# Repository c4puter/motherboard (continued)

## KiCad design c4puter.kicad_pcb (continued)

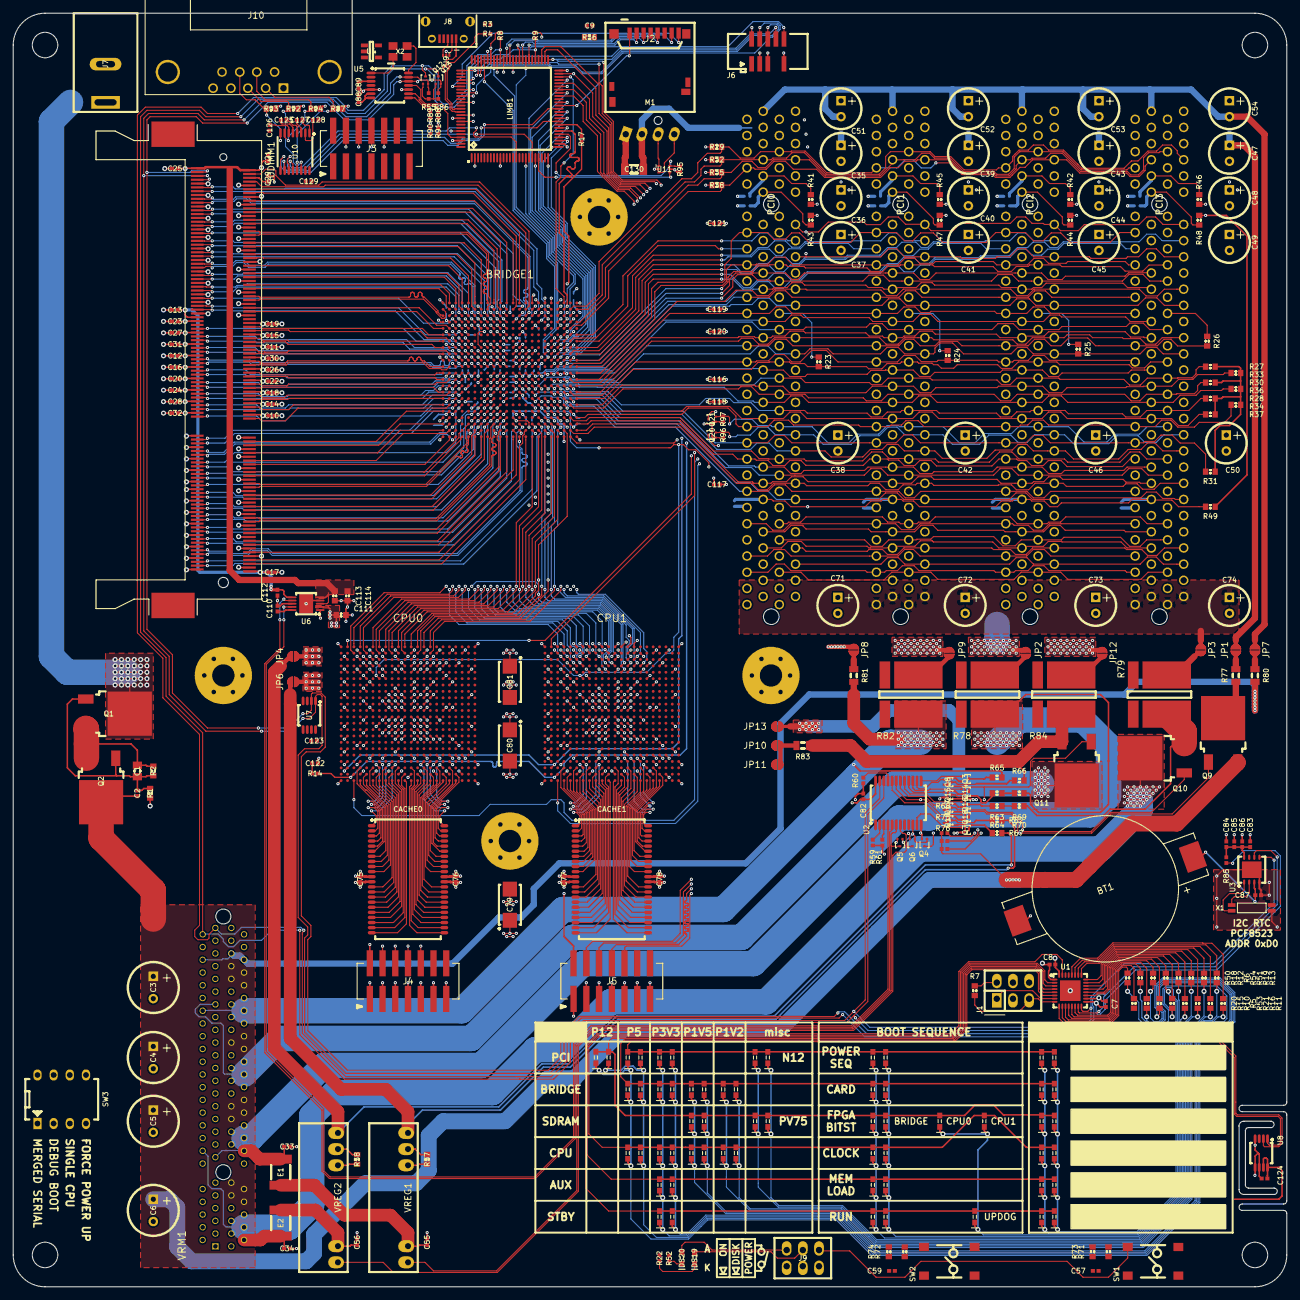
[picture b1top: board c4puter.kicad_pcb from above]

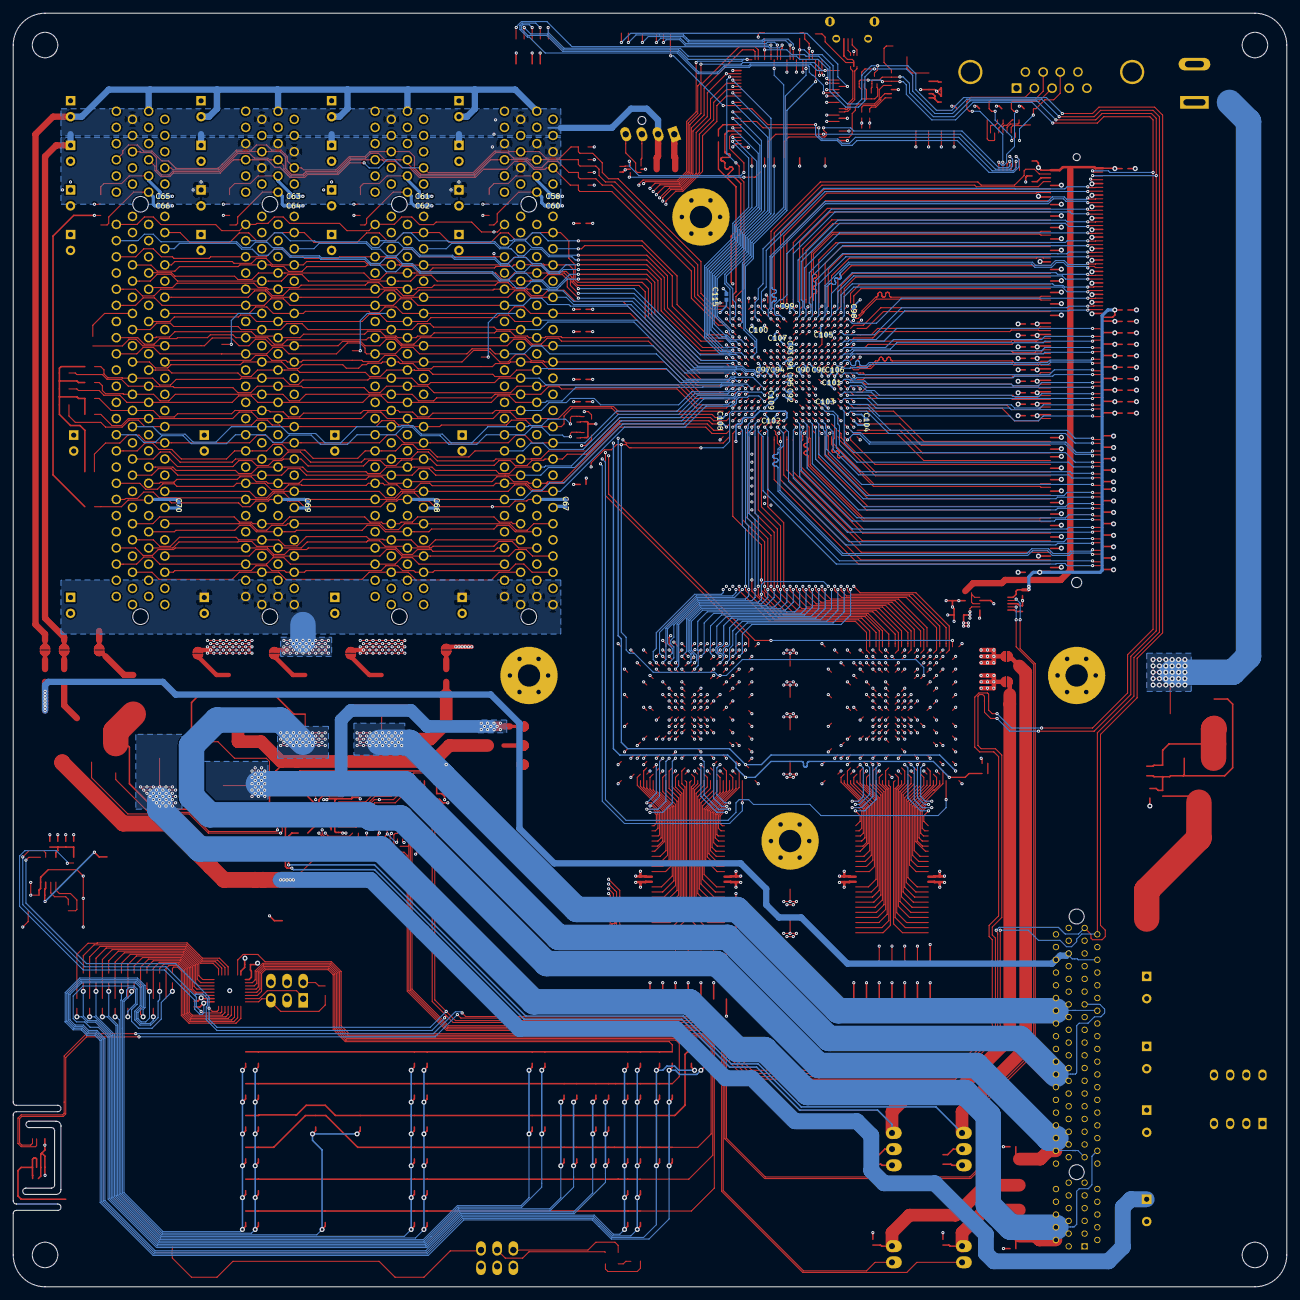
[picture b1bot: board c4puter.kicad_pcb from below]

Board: 6 copper layers, 200.0 x 200.0 mm, 374 parts (40 on the bottom side), 538 nets.

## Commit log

2016-07-06 Finish power supplies
2016-07-06 Upgrade FPGA size, re-route SDRAM
2016-07-06 More PCI work
2016-07-06 Continue routing PCI
2016-07-06 Begin implementing PCI
2016-07-06 Begin replacing power supply
2016-07-06 More power supply work
2016-07-06 PCI bus decoupling
2016-07-06 Uh, more misc work.
2016-07-07 MOAR WORK
2016-07-09 MOAR WORK, v2
2016-07-09 Rip up SDRAM and rotate FPGA
2016-07-10 Reroute SDRAM after bank swap
2016-07-10 Route EC and half of PCI bus to bridge
2016-07-10 Finish routing PCI
2016-07-10 Break out CPU bus
2016-07-10 Add temporary CPU bus pinout file
2016-07-22 workworkwork
2016-07-22 workworkworkwork
2016-07-24 Route CPU bus and cache
2016-07-29 power, yo
2016-08-01 TODO: learn to write good commit messages
2016-08-01 Rearrange power control circuit
2016-08-02 Route clocks
2016-08-02 Proper coin cell holder
2016-08-03 MOAR ROUTING
2016-08-03 Change USB input circuit
2016-08-04 Add RS-232
2016-08-05 Add CPU fan
2016-08-05 Add SDRAM SPD to I2C
2016-08-05 Replace ULN2003 with FETs
2016-08-05 Route PCI SMBUS
2016-08-05 Route PCI utility lines
2016-08-05 Quick TODO revision
2016-08-05 Add configuration pullup resistors
2016-08-05 Tidy up page Power
2016-08-06 Tidy up Power Distribution page
2016-08-06 Approve PCI page with no tidying
2016-08-06 Rename Multibridge to Northbridge
2016-08-06 Tidy up Northbridge sheet
2016-08-06 Tidy up Misc sheet
2016-08-06 Tidy up EC sheet
2016-08-06 Rename EC sheet to LIMB
2016-08-06 Tidy up CPU sheet
2016-08-06 Tidy up Blinkenlights sheet
2016-08-06 Tidy up root sheet
2016-08-06 gitignore .bck files
2016-08-06 Rename project to 'motherboard'
2016-08-06 Fix voltage regulator trim resistors
2016-08-06 Remove unneeded discharge FETs
    PCF8575 can sink the current directly
2016-08-06 Finish adding config interface pullups
2016-08-06 Route FPGA suspend signals
2016-08-06 Add inter-CPU handshake lines
2016-08-06 Move voltage sense to after power routing
2016-08-06 Fix footprint errors and adjust DE-9 footprint
2016-08-06 Check SD and power footprints
2016-08-06 Finish LIMB-SD interface
2016-08-06 Switch resistors to 0402
2016-08-07 Label LIMB sheet
2016-08-08 Rename active-low signals for consistency
2016-08-08 Connect SDRAM EVENT# line
2016-08-08 Route unused PCI JTAG lines
2016-08-10 Add voltage reference
2016-08-10 Update schlib
2016-08-10 Gather and assign all I2C addresses
2016-08-10 Route I2C to CPUs for debug/boot control
    This will provide an interface for the LIMB to write to CPU registers, which
    will be required at least for configuring the program counter at boot.
2016-08-10 Add items to todo list
2016-08-11 Set I2C pullups
2016-08-11 Switch to 8-position DIP switch
2016-08-11 Put clock battery at 180deg orientation for mewyn.
2016-08-11 Add high-speed termination to FPGA config data
    Simulation shows this damping refections.
2016-08-11 Connect RTC alarm interrupt
2016-08-11 Add power connector for storage device
2016-08-11 Set DIP switch part number and courtyard
2016-08-11 IO expander for switches/buttons/LEDs
2016-08-11 Route P3V3_SUSP
2016-08-11 Route P3V3_AUX and some ground
2016-08-11 Route P3V3_BRIDGE
2016-08-11 Route P3V3_CPU
2016-08-11 Add copper fills for connections to VRM
2016-08-11 Route ground
2016-08-11 Route ground, some routing cleanups
2016-08-12 Misc DRC and connectivity fixes
2016-08-12 CPU decoupling
2016-08-12 More power/decoupling
2016-08-12 Add CPUID resistors
2016-08-12 Layer 4 planes
2016-08-12 Route and decouple SDRAM VREF for bridge
2016-08-12 Rest of the planes
2016-08-12 Thermal pads
2016-08-12 Add voltage sense for several rails
2016-08-12 Run ERC and connect missing D6
2016-08-12 Ground plane touchups
2016-08-12 Length-tune SDRAM
2016-08-12 Add more mounting holes
2016-08-12 Length-tune PCI and CPU buses
2016-08-12 Renumber sheets
2016-08-13 Squiggles! Silk!
2016-08-13 Initial BOM
2016-08-14 Final BOM
2016-08-14 Add damping resistor to power input circuit
2016-08-16 Fuck. Rip up bridge.
2016-08-19 Add layer legend
2016-08-19 Fix mechanical pads on SODIMM
2016-08-19 Remove current sense resistors, add I2C debug header
2016-08-19 Via stitching around ground input
2016-08-19 Routing cleanups
2016-08-20 Switch LED metrix driver
2016-08-20 SDRAM take 3: initial breakout
2016-08-21 sdram weeeee
2016-08-23 Reroute CPU bus
2016-08-23 Length-match SDRAM....again
2016-08-25 Route some PCIs
2016-08-28 Route PCI bus. again.
2016-08-29 Redecoupling
2016-08-29 Route bridge JTAG
2016-08-31 Finish most redone routing
2016-08-31 Adjust aux signals, tune FPGA config track lengths
2016-08-31 Fixup PCI power
2016-08-31 Hide silkscreen for 0201 capacitors
2016-08-31 Add some test points
2016-08-31 Add ground clips
2016-09-01 Rearrange LEDs a bit, switch to al-poly caps
2016-09-01 Add some labels
2016-09-01 Make shit pass DRC
2016-09-01 Fix more shit for to pass ERC
2016-09-04 Fix fuckup 2: bank 0 ain't got no SSTL
2016-09-04 Add power input protection
    - Add a fast-blow 6A fuse
    - Specify an optional slow-blow if the fast-blow blows
    - Add snubber near input to damp resonances and prevent spikes
2016-09-05 Redo SDRAM, CPU length matching
2016-09-05 Beeeeeeeeeeeeeeeeeeeeeeeeeeeeeeeeep
2016-09-05 Tidy up a bit
2016-09-05 Final touchup, DRC, render for fab
2016-09-06 Fucking KiCad
2016-09-16 Prepare assembly diagram
2016-09-16 Tidy schematics and produce PDF
2016-09-17 Update library submodule
2016-09-28 Update submodules
2017-10-18 Some stuff?
2017-10-18 Add license
2017-11-18 Update for KiCad 5
2017-11-18 Fix IO expanders (symbol changed in library)
2017-11-18 Update schematic to reflect modifications
2017-12-02 Fix LED address
